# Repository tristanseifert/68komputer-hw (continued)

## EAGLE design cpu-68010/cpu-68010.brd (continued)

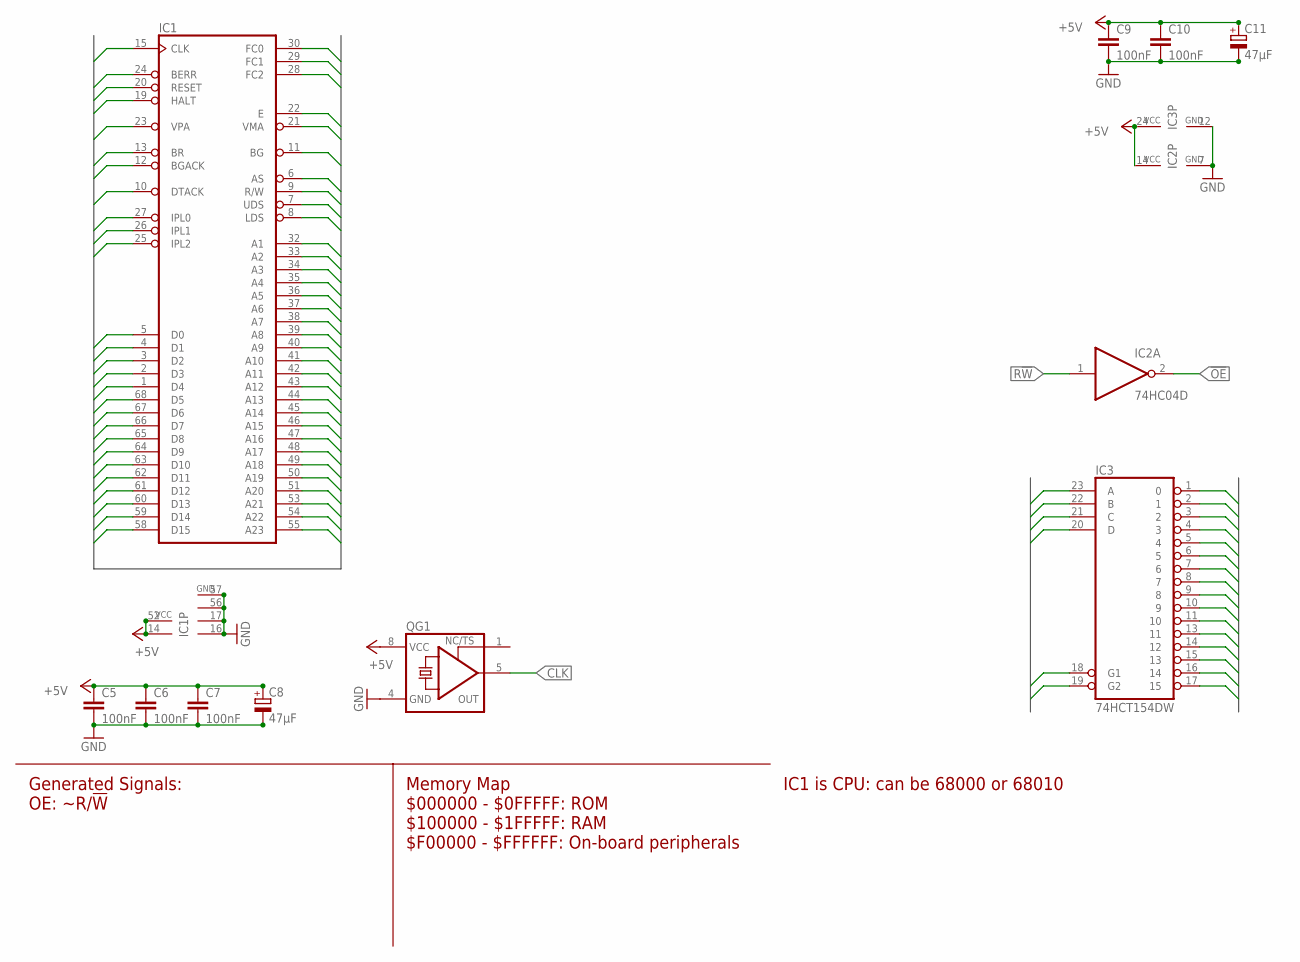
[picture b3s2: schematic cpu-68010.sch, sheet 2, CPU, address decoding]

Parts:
C5, C6, C7, C9, C10: 100nF; C0805; MOUSER 710-885012207072
C8, C11: 47µF; CT6032; MOUSER 581-TAJD476M016RNJV
IC1: MC68000FN-SOC; PLCC68SOCK
IC2: 74HC04D; SO14
IC3: 74HCT154DW; SO24W
QG1: XO-8; DIL08S

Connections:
!AS: IC1.6 (AS); also elsewhere on the board
!BERR: IC1.24 (BERR); also elsewhere on the board
!BG: IC1.11 (BG); also elsewhere on the board
!BGACK: IC1.12 (BGACK); also elsewhere on the board
!BR: IC1.13 (BR); also elsewhere on the board
!DTACK: IC1.10 (DTACK); also elsewhere on the board
!HALT: IC1.19 (HALT); also elsewhere on the board
!IPL0: IC1.27 (IPL0); also elsewhere on the board
!IPL1: IC1.26 (IPL1); also elsewhere on the board
!IPL2: IC1.25 (IPL2); also elsewhere on the board
!LDS: IC1.8 (LDS); also elsewhere on the board
!OE: IC2.2 (O); also elsewhere on the board
!REGION0: IC3.1 (0); also elsewhere on the board
!REGION1: IC3.2 (1); also elsewhere on the board
!REGION2: IC3.3 (2)
!REGION3: IC3.4 (3)
!REGION4: IC3.5 (4)
!REGION5: IC3.6 (5)
!REGION6: IC3.7 (6)
!REGION7: IC3.8 (7)
!REGION8: IC3.9 (8)
!REGION9: IC3.10 (9)
!REGION10: IC3.11 (10)
!REGION11: IC3.13 (11)
!REGION12: IC3.14 (12)
!REGION13: IC3.15 (13)
!REGION14: IC3.16 (14)
!REGION15: IC3.17 (15); also elsewhere on the board
!RESET: IC1.20 (RESET); also elsewhere on the board
!UDS: IC1.7 (UDS); also elsewhere on the board
!VMA: IC1.21 (VMA)
!VPA: IC1.23 (VPA); also elsewhere on the board
+5V: C5.1, C6.1, C7.1, C8.+, C9.1, C10.1, C11.+, IC1.14 (VCC), IC1.52 (VCC), IC2.14 (VCC), IC3.24 (VCC), QG1.8 (VCC); also elsewhere on the board
/AS: IC3.18 (G1), IC3.19 (G2)
A1: IC1.32 (A1); also elsewhere on the board
A2: IC1.33 (A2); also elsewhere on the board
A3: IC1.34 (A3); also elsewhere on the board
A4: IC1.35 (A4); also elsewhere on the board
A5: IC1.36 (A5); also elsewhere on the board
A6: IC1.37 (A6); also elsewhere on the board
A7: IC1.38 (A7); also elsewhere on the board
A8: IC1.39 (A8); also elsewhere on the board
A9: IC1.40 (A9); also elsewhere on the board
A10: IC1.41 (A10); also elsewhere on the board
A11: IC1.42 (A11); also elsewhere on the board
A12: IC1.43 (A12); also elsewhere on the board
A13: IC1.44 (A13); also elsewhere on the board
A14: IC1.45 (A14); also elsewhere on the board
A15: IC1.46 (A15); also elsewhere on the board
A16: IC1.47 (A16); also elsewhere on the board
A17: IC1.48 (A17); also elsewhere on the board
A18: IC1.49 (A18); also elsewhere on the board
A19: IC1.50 (A19); also elsewhere on the board
A20: IC1.51 (A20), IC3.23 (A); also elsewhere on the board
A21: IC1.53 (A21), IC3.22 (B); also elsewhere on the board
A22: IC1.54 (A22), IC3.21 (C); also elsewhere on the board
A23: IC1.55 (A23), IC3.20 (D); also elsewhere on the board
CLK: IC1.15 (CLK), QG1.5 (OUT); also elsewhere on the board
D0: IC1.5 (D0); also elsewhere on the board
D1: IC1.4 (D1); also elsewhere on the board
D2: IC1.3 (D2); also elsewhere on the board
D3: IC1.2 (D3); also elsewhere on the board
D4: IC1.1 (D4); also elsewhere on the board
D5: IC1.68 (D5); also elsewhere on the board
D6: IC1.67 (D6); also elsewhere on the board
D7: IC1.66 (D7); also elsewhere on the board
D8: IC1.65 (D8); also elsewhere on the board
D9: IC1.64 (D9); also elsewhere on the board
D10: IC1.63 (D10); also elsewhere on the board
D11: IC1.62 (D11); also elsewhere on the board
D12: IC1.61 (D12); also elsewhere on the board
D13: IC1.60 (D13); also elsewhere on the board
D14: IC1.59 (D14); also elsewhere on the board
D15: IC1.58 (D15); also elsewhere on the board
E: IC1.22 (E)
FC0: IC1.30 (FC0); also elsewhere on the board
FC1: IC1.29 (FC1); also elsewhere on the board
FC2: IC1.28 (FC2); also elsewhere on the board
GND: C5.2, C6.2, C7.2, C8.-, C9.2, C10.2, C11.-, IC1.16 (GND), IC1.17 (GND), IC1.56 (GND), IC1.57 (GND), IC2.7 (GND), IC3.12 (GND), QG1.4 (GND); also elsewhere on the board
R!W!: IC1.9 (R/W), IC2.1 (I); also elsewhere on the board

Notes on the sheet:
IC1 is CPU: can be 68000 or 68010
Memory Map $000000 - $0FFFFF: ROM $100000 - $1FFFFF: RAM $F00000 - $FFFFFF: On-board peripherals
Generated Signals: OE: ~R/!W

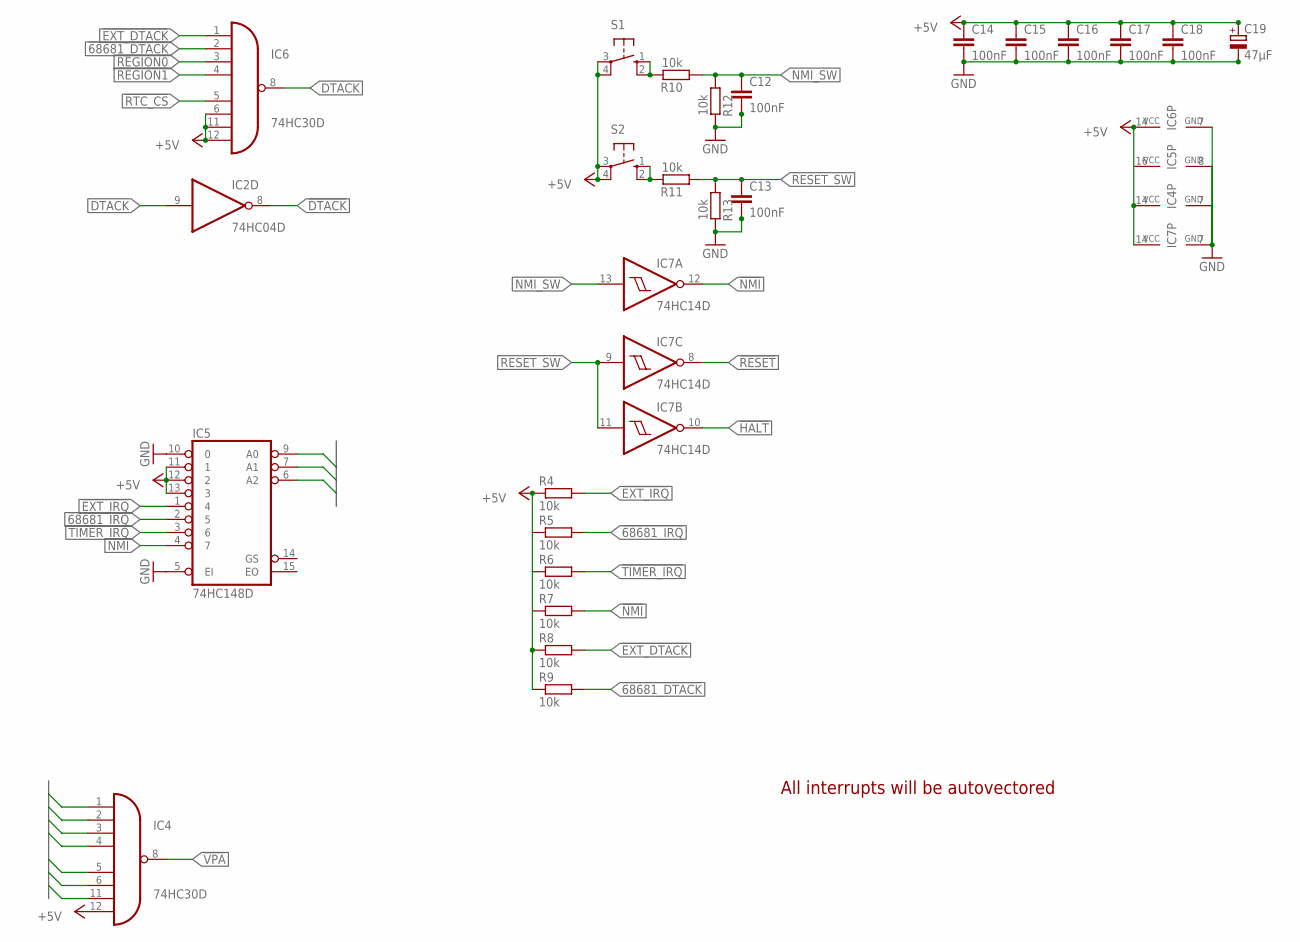
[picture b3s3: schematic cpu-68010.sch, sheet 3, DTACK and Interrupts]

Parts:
C12, C13, C14, C15, C16, C17, C18: 100nF; C0805; MOUSER 710-885012207072
C19: 47µF; CT6032; MOUSER 581-TAJD476M016RNJV
IC2: 74HC04D; SO14
IC4, IC6: 74HC30D; SO14
IC5: 74HC148D; SO16
IC7: 74HC14D; SO14
R4, R5, R6, R7, R8, R9, R10, R11, R12, R13: 10k; M0805; MOUSER 652-CR0805-FX6800GLF
S1, S2: 10-XX; B3F-10XX

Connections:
!68681_DTACK: IC6.2 (I1), R9.2; also elsewhere on the board
!68681_IRQ: IC5.2 (5), R5.2; also elsewhere on the board
!DTACK: IC2.8 (O); also elsewhere on the board
!EXT_DTACK: IC6.1 (I0), R8.2; also elsewhere on the board
!EXT_IRQ: IC5.1 (4), R4.2; also elsewhere on the board
!HALT: IC7.10 (O); also elsewhere on the board
!IPL0: IC5.9 (A0); also elsewhere on the board
!IPL1: IC5.7 (A1); also elsewhere on the board
!IPL2: IC5.6 (A2); also elsewhere on the board
!NMI: IC5.4 (7), IC7.12 (O), R7.2
!REGION0: IC6.3 (I2); also elsewhere on the board
!REGION1: IC6.4 (I3); also elsewhere on the board
!RESET: IC7.8 (O); also elsewhere on the board
!RTC_CS: IC6.5 (I4); also elsewhere on the board
!TIMER_IRQ: IC5.3 (6), R6.2
!VPA: IC4.8 (O); also elsewhere on the board
+5V: C14.1, C15.1, C16.1, C17.1, C18.1, C19.+, IC4.12 (I7), IC4.14 (VCC), IC5.11 (1), IC5.12 (2), IC5.13 (3), IC5.16 (VCC), IC6.6 (I5), IC6.11 (I6), IC6.12 (I7), IC6.14 (VCC), IC7.14 (VCC), R4.1, R8.1, R9.1, S1.3, S1.4 (P1), S2.3, S2.4 (P1); also elsewhere on the board
A16: IC4.4 (I3); also elsewhere on the board
A17: IC4.5 (I4); also elsewhere on the board
A18: IC4.6 (I5); also elsewhere on the board
A19: IC4.11 (I6); also elsewhere on the board
DTACK: IC2.9 (I), IC6.8 (O)
FC0: IC4.1 (I0); also elsewhere on the board
FC1: IC4.2 (I1); also elsewhere on the board
FC2: IC4.3 (I2); also elsewhere on the board
GND: C12.2, C13.2, C14.2, C15.2, C16.2, C17.2, C18.2, C19.-, IC4.7 (GND), IC5.5 (EI), IC5.8 (GND), IC5.10 (0), IC6.7 (GND), IC7.7 (GND), R12.2, R13.2; also elsewhere on the board
unnamed: R11.2, S2.1 (S), S2.2 (S1)
unnamed: R10.2, S1.1 (S), S1.2 (S1)
NMI_SW: C12.1, IC7.13 (I), R10.1, R12.1
RESET_SW: C13.1, IC7.9 (I), IC7.11 (I), R11.1, R13.1

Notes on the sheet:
All interrupts will be autovectored

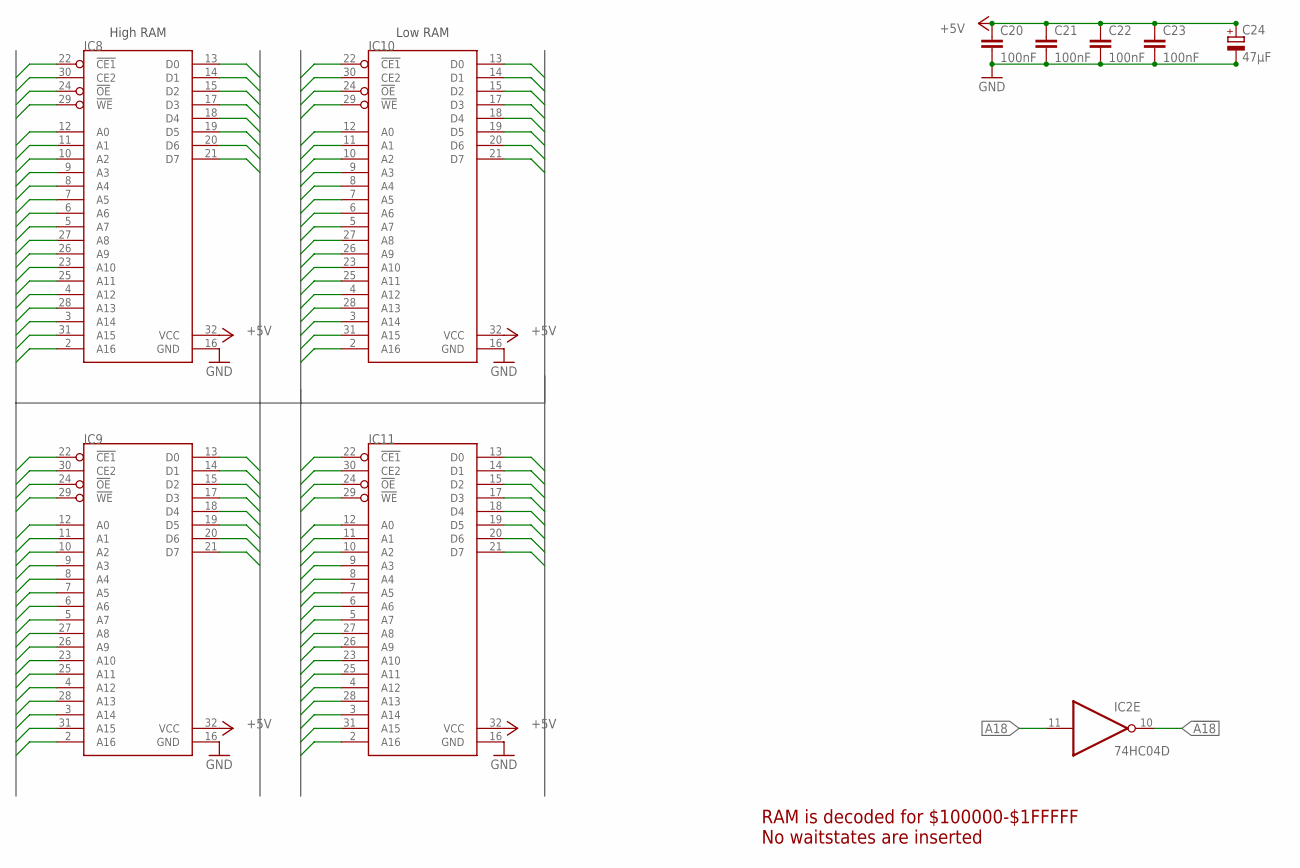
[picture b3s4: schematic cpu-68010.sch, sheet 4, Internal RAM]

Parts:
C20, C21, C22, C23: 100nF; C0805; MOUSER 710-885012207072
C24: 47µF; CT6032; MOUSER 581-TAJD476M016RNJV
IC2: 74HC04D; SO14
IC8, IC9, IC10, IC11: CY62128BSOIC32; SO32X

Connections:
!A18: IC2.10 (O), IC8.30 (CE2), IC9.30 (CE2), IC10.30 (CE2), IC11.30 (CE2)
!OE: IC8.24 (!OE), IC9.24 (!OE), IC10.24 (!OE), IC11.24 (!OE); also elsewhere on the board
!REGION1: IC8.22 (!CE1), IC9.22 (!CE1), IC10.22 (!CE1), IC11.22 (!CE1); also elsewhere on the board
+5V: C20.1, C21.1, C22.1, C23.1, C24.+, IC8.32 (VCC), IC9.32 (VCC), IC10.32 (VCC), IC11.32 (VCC); also elsewhere on the board
A1: IC8.12 (A0), IC9.12 (A0), IC10.12 (A0), IC11.12 (A0); also elsewhere on the board
A2: IC8.11 (A1), IC9.11 (A1), IC10.11 (A1), IC11.11 (A1); also elsewhere on the board
A3: IC8.10 (A2), IC9.10 (A2), IC10.10 (A2), IC11.10 (A2); also elsewhere on the board
A4: IC8.9 (A3), IC9.9 (A3), IC10.9 (A3), IC11.9 (A3); also elsewhere on the board
A5: IC8.8 (A4), IC9.8 (A4), IC10.8 (A4), IC11.8 (A4); also elsewhere on the board
A6: IC8.7 (A5), IC9.7 (A5), IC10.7 (A5), IC11.7 (A5); also elsewhere on the board
A7: IC8.6 (A6), IC9.6 (A6), IC10.6 (A6), IC11.6 (A6); also elsewhere on the board
A8: IC8.5 (A7), IC9.5 (A7), IC10.5 (A7), IC11.5 (A7); also elsewhere on the board
A9: IC8.27 (A8), IC9.27 (A8), IC10.27 (A8), IC11.27 (A8); also elsewhere on the board
A10: IC8.26 (A9), IC9.26 (A9), IC10.26 (A9), IC11.26 (A9); also elsewhere on the board
A11: IC8.23 (A10), IC9.23 (A10), IC10.23 (A10), IC11.23 (A10); also elsewhere on the board
A12: IC8.25 (A11), IC9.25 (A11), IC10.25 (A11), IC11.25 (A11); also elsewhere on the board
A13: IC8.4 (A12), IC9.4 (A12), IC10.4 (A12), IC11.4 (A12); also elsewhere on the board
A14: IC8.28 (A13), IC9.28 (A13), IC10.28 (A13), IC11.28 (A13); also elsewhere on the board
A15: IC8.3 (A14), IC9.3 (A14), IC10.3 (A14), IC11.3 (A14); also elsewhere on the board
A16: IC8.31 (A15), IC9.31 (A15), IC10.31 (A15), IC11.31 (A15); also elsewhere on the board
A17: IC8.2 (A16), IC9.2 (A16), IC10.2 (A16), IC11.2 (A16); also elsewhere on the board
A18: IC2.11 (I); also elsewhere on the board
D0: IC10.13 (D0), IC11.13 (D0); also elsewhere on the board
D1: IC10.14 (D1), IC11.14 (D1); also elsewhere on the board
D2: IC10.15 (D2), IC11.15 (D2); also elsewhere on the board
D3: IC10.17 (D3), IC11.17 (D3); also elsewhere on the board
D4: IC10.18 (D4), IC11.18 (D4); also elsewhere on the board
D5: IC10.19 (D5), IC11.19 (D5); also elsewhere on the board
D6: IC10.20 (D6), IC11.20 (D6); also elsewhere on the board
D7: IC10.21 (D7), IC11.21 (D7); also elsewhere on the board
D8: IC8.13 (D0), IC9.13 (D0); also elsewhere on the board
D9: IC8.14 (D1), IC9.14 (D1); also elsewhere on the board
D10: IC8.15 (D2), IC9.15 (D2); also elsewhere on the board
D11: IC8.17 (D3), IC9.17 (D3); also elsewhere on the board
D12: IC8.18 (D4), IC9.18 (D4); also elsewhere on the board
D13: IC8.19 (D5), IC9.19 (D5); also elsewhere on the board
D14: IC8.20 (D6), IC9.20 (D6); also elsewhere on the board
D15: IC8.21 (D7), IC9.21 (D7); also elsewhere on the board
GND: C20.2, C21.2, C22.2, C23.2, C24.-, IC8.16 (GND), IC9.16 (GND), IC10.16 (GND), IC11.16 (GND); also elsewhere on the board
R/!W!: IC8.29 (!WE), IC9.29 (!WE), IC10.29 (!WE), IC11.29 (!WE); also elsewhere on the board

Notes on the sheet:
RAM is decoded for $100000-$1FFFFF No waitstates are inserted
High RAM
Low RAM

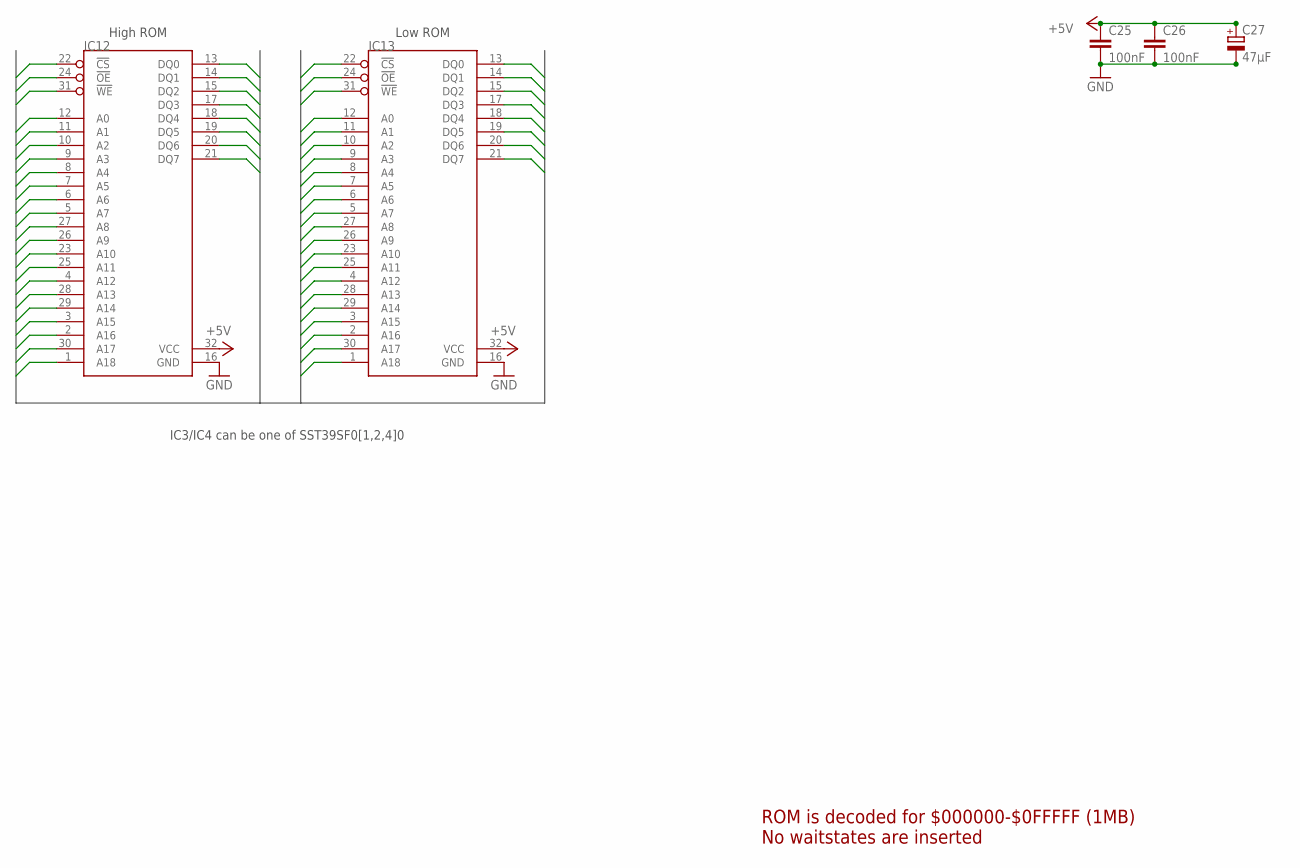
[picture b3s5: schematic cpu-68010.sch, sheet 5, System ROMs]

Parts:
C25, C26: 100nF; C0805; MOUSER 710-885012207072
C27: 47µF; CT6032; MOUSER 581-TAJD476M016RNJV
IC12, IC13: SST39SF0X0PDIP32; DIL32

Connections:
!OE: IC12.24 (!OE), IC13.24 (!OE); also elsewhere on the board
!REGION0: IC12.22 (!CS), IC13.22 (!CS); also elsewhere on the board
+5V: C25.1, C26.1, C27.+, IC12.32 (VCC), IC13.32 (VCC); also elsewhere on the board
A1: IC12.12 (A0), IC13.12 (A0); also elsewhere on the board
A2: IC12.11 (A1), IC13.11 (A1); also elsewhere on the board
A3: IC12.10 (A2), IC13.10 (A2); also elsewhere on the board
A4: IC12.9 (A3), IC13.9 (A3); also elsewhere on the board
A5: IC12.8 (A4), IC13.8 (A4); also elsewhere on the board
A6: IC12.7 (A5), IC13.7 (A5); also elsewhere on the board
A7: IC12.6 (A6), IC13.6 (A6); also elsewhere on the board
A8: IC12.5 (A7), IC13.5 (A7); also elsewhere on the board
A9: IC12.27 (A8), IC13.27 (A8); also elsewhere on the board
A10: IC12.26 (A9), IC13.26 (A9); also elsewhere on the board
A11: IC12.23 (A10), IC13.23 (A10); also elsewhere on the board
A12: IC12.25 (A11), IC13.25 (A11); also elsewhere on the board
A13: IC12.4 (A12), IC13.4 (A12); also elsewhere on the board
A14: IC12.28 (A13), IC13.28 (A13); also elsewhere on the board
A15: IC12.29 (A14), IC13.29 (A14); also elsewhere on the board
A16: IC12.3 (A15), IC13.3 (A15); also elsewhere on the board
A17: IC12.2 (A16), IC13.2 (A16); also elsewhere on the board
A18: IC12.30 (A17), IC13.30 (A17); also elsewhere on the board
A19: IC12.1 (A18), IC13.1 (A18); also elsewhere on the board
D0: IC13.13 (DQ0); also elsewhere on the board
D1: IC13.14 (DQ1); also elsewhere on the board
D2: IC13.15 (DQ2); also elsewhere on the board
D3: IC13.17 (DQ3); also elsewhere on the board
D4: IC13.18 (DQ4); also elsewhere on the board
D5: IC13.19 (DQ5); also elsewhere on the board
D6: IC13.20 (DQ6); also elsewhere on the board
D7: IC13.21 (DQ7); also elsewhere on the board
D8: IC12.13 (DQ0); also elsewhere on the board
D9: IC12.14 (DQ1); also elsewhere on the board
D10: IC12.15 (DQ2); also elsewhere on the board
D11: IC12.17 (DQ3); also elsewhere on the board
D12: IC12.18 (DQ4); also elsewhere on the board
D13: IC12.19 (DQ5); also elsewhere on the board
D14: IC12.20 (DQ6); also elsewhere on the board
D15: IC12.21 (DQ7); also elsewhere on the board
GND: C25.2, C26.2, C27.-, IC12.16 (GND), IC13.16 (GND); also elsewhere on the board
R/!W!: IC12.31 (!WE), IC13.31 (!WE); also elsewhere on the board

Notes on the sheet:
High ROM
Low ROM
ROM is decoded for $000000-$0FFFFF (1MB) No waitstates are inserted
IC3/IC4 can be one of SST39SF0[1,2,4]0

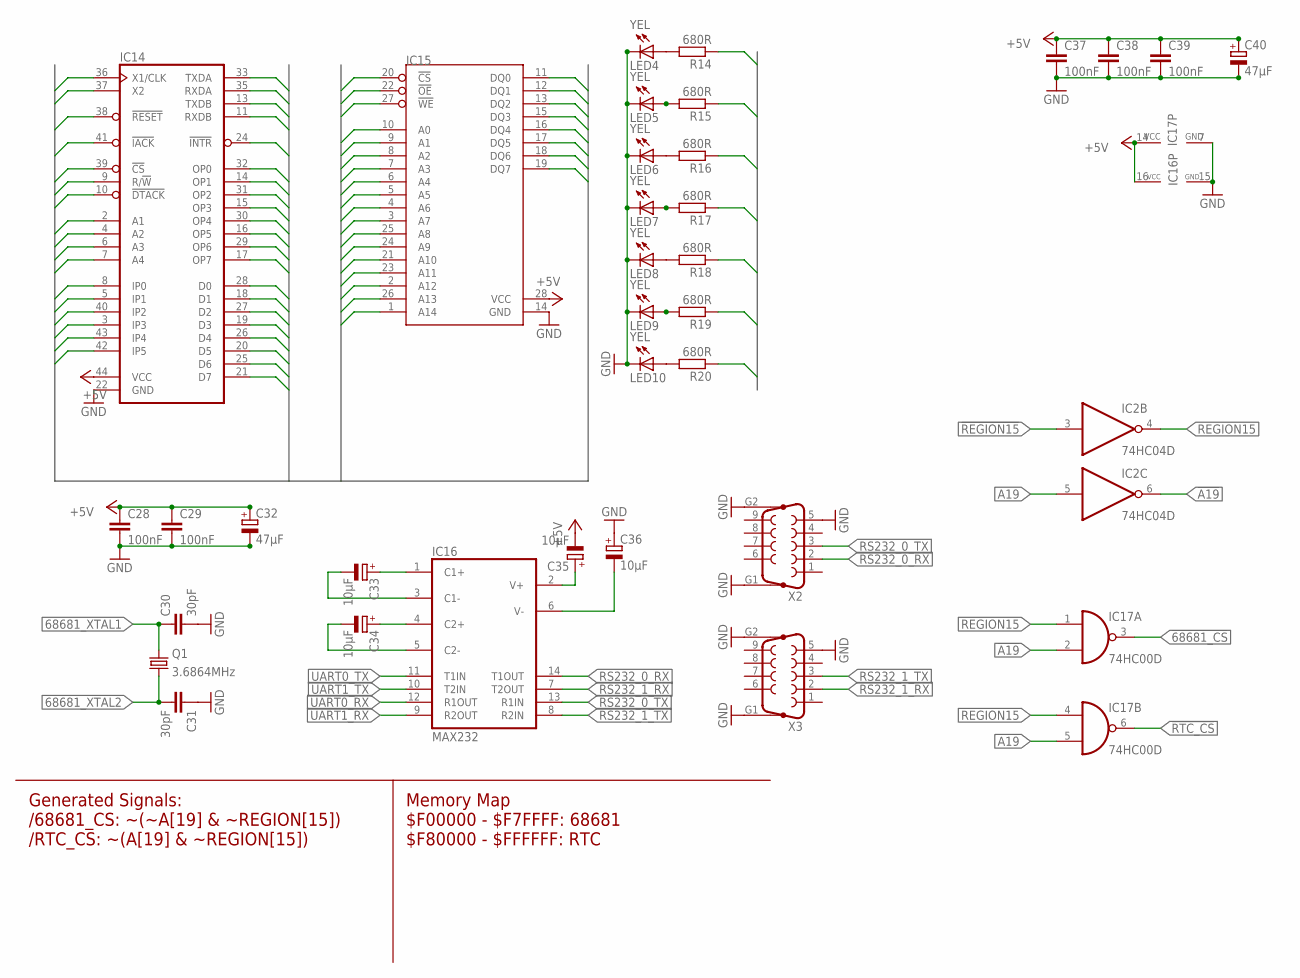
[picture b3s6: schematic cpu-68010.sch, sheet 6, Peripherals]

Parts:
C28, C29, C37, C38, C39: 100nF; C0805; MOUSER 710-885012207072
C30, C31: 30pF; C0805; MOUSER 710-885012207072
C32, C40: 47µF; CT6032; MOUSER 581-TAJD476M016RNJV
C33, C34, C35, C36: 10µF; E1,8-4
IC2: 74HC04D; SO14
IC14: MC68681PLCC44-SOCKET; PLCC-S44
IC15: DS1244EDIP-28; DIL28-6
IC16: MAX232; DIL16
IC17: 74HC00D; SO14
LED4, LED5, LED6, LED7, LED8, LED9, LED10: YEL; CHIPLED_1206; MOUSER 710-156120YS75300
Q1: 3.6864MHz; HC49/S
R14, R15, R16, R17, R18, R19, R20: 680R; M0805; MOUSER 652-CR0805-FX6800GLF
X2, X3: F09HP

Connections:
68681_XTAL1: C30.1, IC14.36 (X1/CLK), Q1.2
68681_XTAL2: C31.2, IC14.37 (X2), Q1.1
!68681_CS: IC14.39 (!CS), IC17.3 (O)
!68681_DTACK: IC14.10 (!DTACK); also elsewhere on the board
!68681_IRQ: IC14.24 (!INTR); also elsewhere on the board
!68681_IRQACK: IC14.41 (!IACK)
!A19: IC2.6 (O), IC17.2 (I1)
!OE: IC15.22 (!OE); also elsewhere on the board
!REGION15: IC2.3 (I); also elsewhere on the board
!RESET: IC14.38 (!RESET); also elsewhere on the board
!RTC_CS: IC15.20 (!CS), IC17.6 (O); also elsewhere on the board
+5V: C28.1, C29.1, C32.+, C35.-, C37.1, C38.1, C39.1, C40.+, IC14.44 (VCC), IC15.28 (VCC), IC16.16 (VCC), IC17.14 (VCC); also elsewhere on the board
A1: IC14.2 (A1), IC15.10 (A0); also elsewhere on the board
A2: IC14.4 (A2), IC15.9 (A1); also elsewhere on the board
A3: IC14.6 (A3), IC15.8 (A2); also elsewhere on the board
A4: IC14.7 (A4), IC15.7 (A3); also elsewhere on the board
A5: IC15.6 (A4); also elsewhere on the board
A6: IC15.5 (A5); also elsewhere on the board
A7: IC15.4 (A6); also elsewhere on the board
A8: IC15.3 (A7); also elsewhere on the board
A9: IC15.25 (A8); also elsewhere on the board
A10: IC15.24 (A9); also elsewhere on the board
A11: IC15.21 (A10); also elsewhere on the board
A12: IC15.23 (A11); also elsewhere on the board
A13: IC15.2 (A12); also elsewhere on the board
A14: IC15.26 (A13); also elsewhere on the board
A15: IC15.1 (A14); also elsewhere on the board
A19: IC2.5 (I), IC17.5 (I1); also elsewhere on the board
D0: IC14.28 (D0), IC15.11 (DQ0); also elsewhere on the board
D1: IC14.18 (D1), IC15.12 (DQ1); also elsewhere on the board
D2: IC14.27 (D2), IC15.13 (DQ2); also elsewhere on the board
D3: IC14.19 (D3), IC15.15 (DQ3); also elsewhere on the board
D4: IC14.26 (D4), IC15.16 (DQ4); also elsewhere on the board
D5: IC14.20 (D5), IC15.17 (DQ5); also elsewhere on the board
D6: IC14.25 (D6), IC15.18 (DQ6); also elsewhere on the board
D7: IC14.21 (D7), IC15.19 (DQ7); also elsewhere on the board
GND: C28.2, C29.2, C30.2, C31.1, C32.-, C36.+, C37.2, C38.2, C39.2, C40.-, IC14.22 (GND), IC15.14 (GND), IC16.15 (GND), IC17.7 (GND), LED4.C, LED5.C, LED6.C, LED7.C, LED8.C, LED9.C, LED10.C, X2.5, X2.G1, X2.G2, X3.5, X3.G1, X3.G2; also elsewhere on the board
GPIO_IN0: IC14.8 (IP0)
GPIO_IN1: IC14.5 (IP1)
GPIO_IN2: IC14.40 (IP2)
GPIO_IN3: IC14.3 (IP3)
GPIO_IN4: IC14.43 (IP4)
GPIO_IN5: IC14.42 (IP5)
GPIO_OUT0: IC14.32 (OP0), R14.1
GPIO_OUT1: IC14.14 (OP1), R15.1
GPIO_OUT2: IC14.15 (OP3), R16.1
GPIO_OUT3: IC14.30 (OP4), R17.1
GPIO_OUT4: IC14.16 (OP5), R18.1
GPIO_OUT5: IC14.29 (OP6), R19.1
GPIO_OUT6: IC14.17 (OP7), R20.1
unnamed: C35.+, IC16.2 (V+)
unnamed: C36.-, IC16.6 (V-)
unnamed: C33.+, IC16.1 (C1+)
unnamed: C34.+, IC16.4 (C2+)
unnamed: C33.-, IC16.3 (C1-)
unnamed: C34.-, IC16.5 (C2-)
unnamed: LED9.A, R19.2
unnamed: LED8.A, R18.2
unnamed: LED7.A, R17.2
unnamed: LED6.A, R16.2
unnamed: LED5.A, R15.2
unnamed: LED4.A, R14.2
unnamed: LED10.A, R20.2
R/!W!: IC14.9 (R/!W), IC15.27 (!WE); also elsewhere on the board
REGION15: IC2.4 (O), IC17.1 (I0), IC17.4 (I0)
RS232_0_RX: IC16.14 (T1OUT), X2.2
RS232_0_TX: IC16.13 (R1IN), X2.3
RS232_1_RX: IC16.7 (T2OUT), X3.2
RS232_1_TX: IC16.8 (R2IN), X3.3
TIMER_CLK: IC14.31 (OP2)
UART0_RX: IC14.35 (RXDA), IC16.12 (R1OUT)
UART0_TX: IC14.33 (TXDA), IC16.11 (T1IN)
UART1_RX: IC14.11 (RXDB), IC16.9 (R2OUT)
UART1_TX: IC14.13 (TXDB), IC16.10 (T2IN)

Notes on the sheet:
Memory Map $F00000 - $F7FFFF: 68681 $F80000 - $FFFFFF: RTC
Generated Signals: /68681_CS: ~(~A[19] & ~REGION[15]) /RTC_CS: ~(A[19] & ~REGION[15])

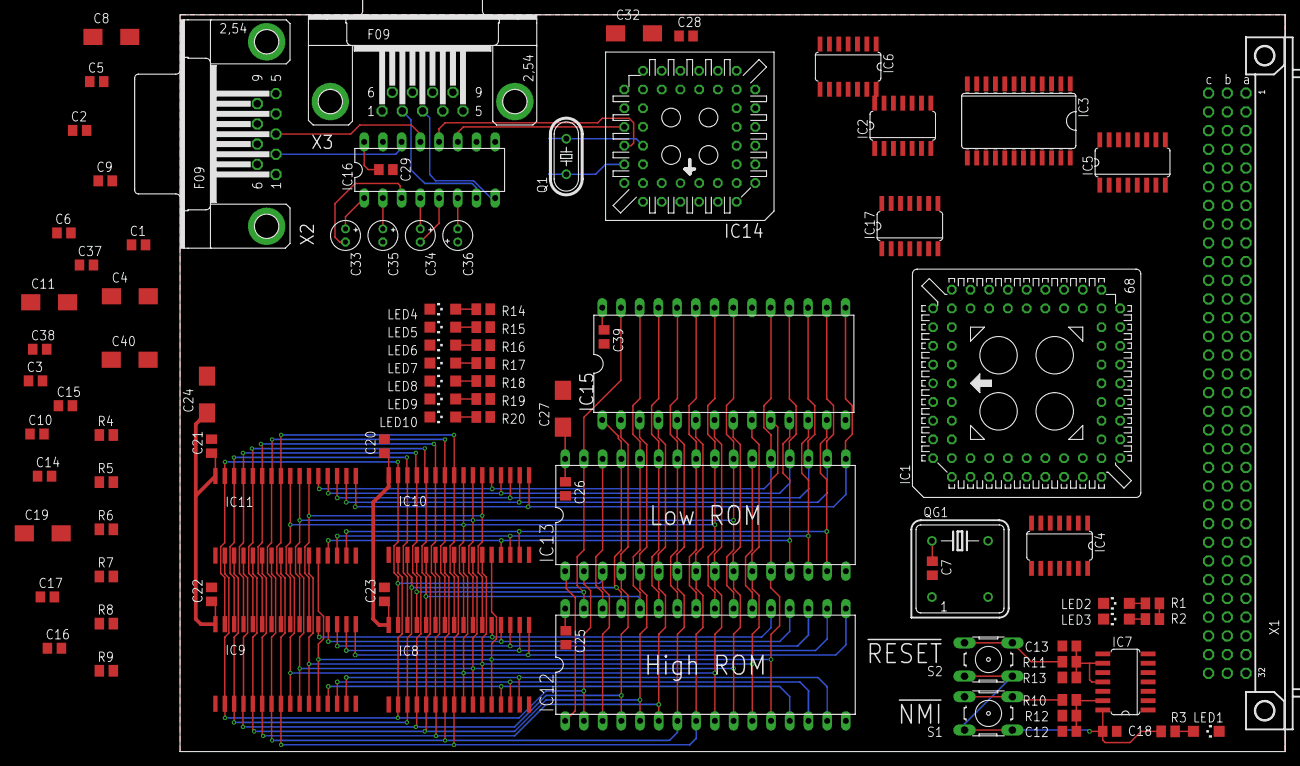
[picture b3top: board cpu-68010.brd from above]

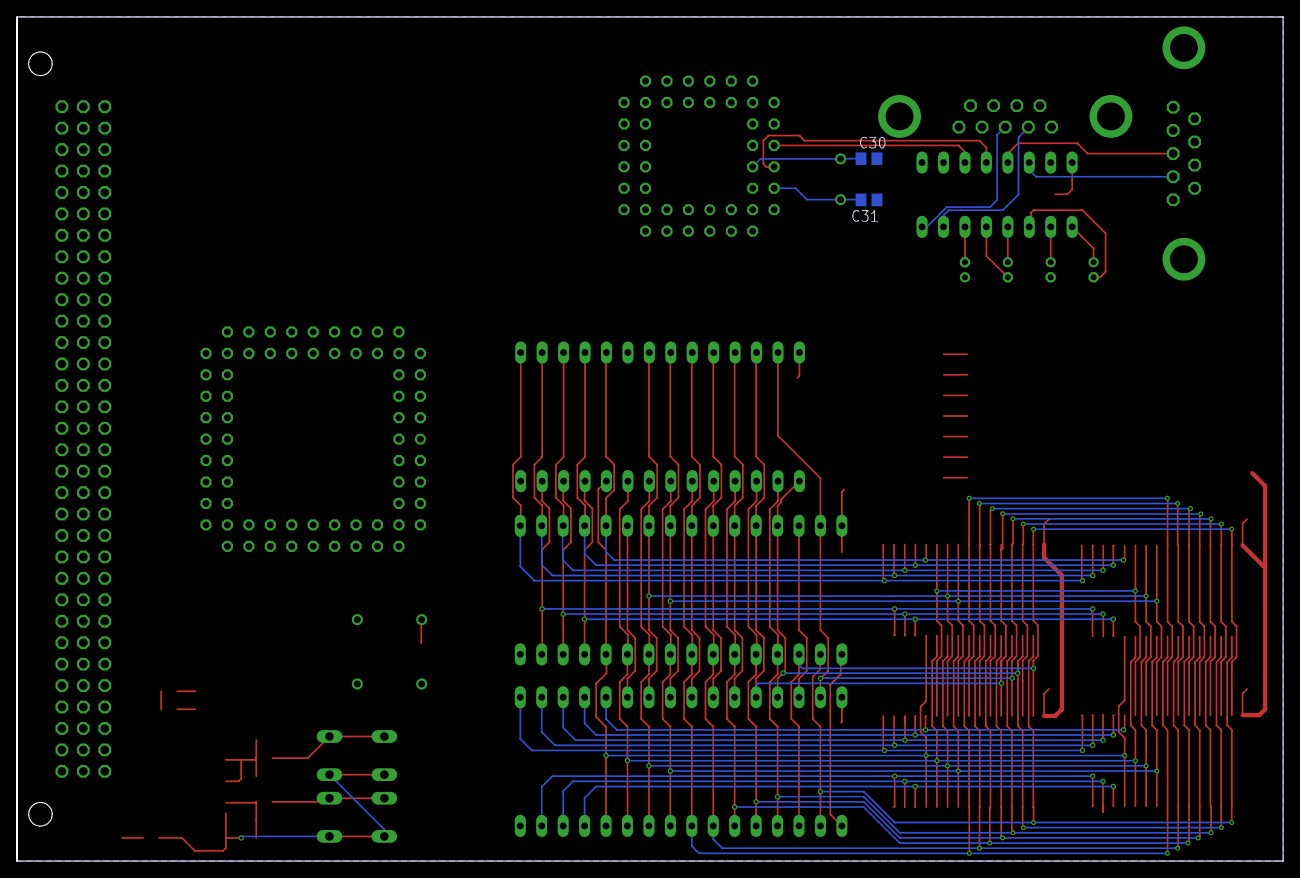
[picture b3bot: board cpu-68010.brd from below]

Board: 2 copper layers, 150.0 x 100.0 mm, 94 parts (2 on the bottom side), 115 nets.
